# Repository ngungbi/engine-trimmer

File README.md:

# Engine Throttle Trimer

This device is used to adjust servo throttle for internal combustion engine from pixhawk output.

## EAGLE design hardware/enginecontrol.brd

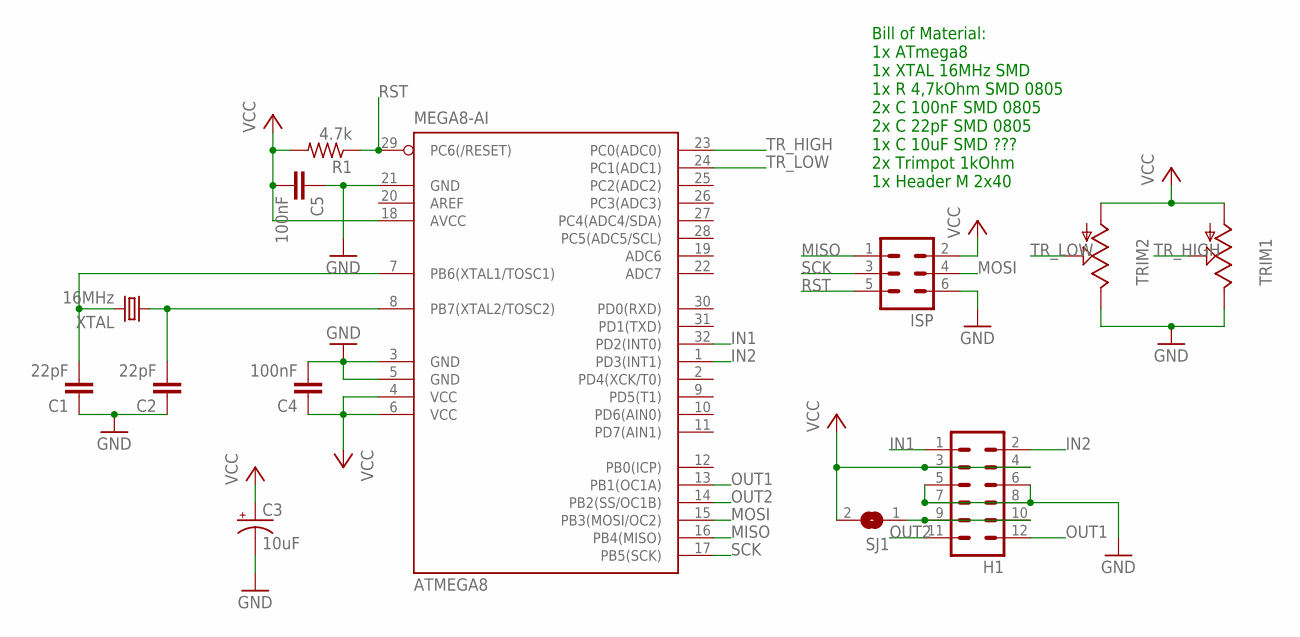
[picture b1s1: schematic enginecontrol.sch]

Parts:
ATMEGA8: MEGA8-AI; TQFP32-08
C1, C2: 22pF; C0805
C3: 10uF; 153CLV-0605
C4, C5: 100nF; C0805
H1: MA06-2
ISP: MA03-2
R1: 4.7k; M0805
SJ1: SJ
TRIM1, TRIM2: TRIM_US-B25P; B25P
XTAL: 16MHz; SM49

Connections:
GND: ATMEGA8.3 (GND), ATMEGA8.5 (GND), ATMEGA8.21 (GND), C1.1, C2.1, C3.-, C4.2, C5.1, H1.5, H1.6, H1.7, H1.8, ISP.6, TRIM1.E, TRIM2.E
IN1: ATMEGA8.32 (PD2(INT0)), H1.1
IN2: ATMEGA8.1 (PD3(INT1)), H1.2
MISO: ATMEGA8.16 (PB4(MISO)), ISP.1
MOSI: ATMEGA8.15 (PB3(MOSI/OC2)), ISP.4
unnamed: ATMEGA8.8 (PB7(XTAL2/TOSC2)), C2.2, XTAL.1
unnamed: ATMEGA8.7 (PB6(XTAL1/TOSC1)), C1.2, XTAL.2
unnamed: H1.9, H1.10, SJ1.1
OUT1: ATMEGA8.13 (PB1(OC1A)), H1.12
OUT2: ATMEGA8.14 (PB2(SS/OC1B)), H1.11
RST: ATMEGA8.29 (PC6(/RESET)), ISP.5, R1.1
SCK: ATMEGA8.17 (PB5(SCK)), ISP.3
TR_HIGH: ATMEGA8.23 (PC0(ADC0)), TRIM1.S
TR_LOW: ATMEGA8.24 (PC1(ADC1)), TRIM2.S
VCC: ATMEGA8.4 (VCC), ATMEGA8.6 (VCC), ATMEGA8.18 (AVCC), C3.+, C4.1, C5.2, H1.3, H1.4, ISP.2, R1.2, SJ1.2, TRIM1.A, TRIM2.A

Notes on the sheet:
Bill of Material: 1x ATmega8 1x XTAL 16MHz SMD 1x R 4,7kOhm SMD 0805 2x C 100nF SMD 0805 2x C 22pF SMD 0805 1x C 10uF SMD ??? 2x Trimpot 1kOhm 1x Header M 2x40

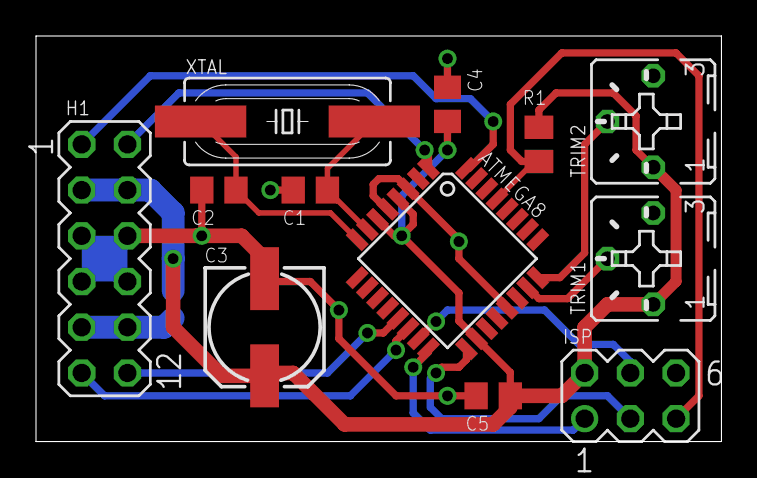
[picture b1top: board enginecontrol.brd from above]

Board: 2 copper layers, 38.1 x 22.5 mm, 13 parts (1 on the bottom side), 15 nets.

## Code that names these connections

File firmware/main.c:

#include <avr/io.h>
#include <avr/interrupt.h>
//#include <avr/eeprom.h>
#include <util/delay.h>
#include <stdint.h>
#include <stdio.h>

#include "adc.h"

#include "config.h"

//volatile uint8_t timerL = 0;
volatile uint8_t timerH = 0;
volatile uint16_t time0 = 0;
volatile uint16_t time1 = 0;

volatile uint16_t trimLow = 0;
volatile uint16_t trimHigh = 0;
volatile uint16_t range = 1000;

volatile uint16_t pwmIn = 2000;
volatile uint16_t pwmOut = 2000;

// manual PWM, adakah cara yang lebih baik? ._.
ISR(TIMER1_OVF_vect){
	PORTB |= (1<<2);
}
ISR(TIMER1_COMPA_vect){
	PORTB &= ~(1<<2);
}

// hitung pwm input
ISR(TIMER0_OVF_vect){
	timerH++;
}
ISR(INT0_vect){
	uint16_t timeNow = ((uint16_t)timerH<<8) | TCNT0;
	
	if( PIND&(1<<2) ){ // awal sinyal pwm
		PORTB |= (1<<1); // passthru
		time0 = timeNow;
	}else{ // akhir sinyal pwm
		PORTB &= ~(1<<1);
		time1 = timeNow;
		pwmIn = (time1-time0);

		// kasih batas nilai
		if(pwmIn<2000) pwmIn = 2000;
		else if(pwmIn>4000) pwmIn = 4000;

		// remap
		float value = (float)(pwmIn-2000)/2000.0 * range;
		pwmOut = (uint16_t)value + 2000 + trimLow;
		OCR1A = pwmOut;
	}
}

int main( void ){

	DDRB = 0x00;
	DDRC = 0x00;

	// input di PD2 dan PD3 (INT0, INT1)
	DDRD = 0x00;

	// output di PB1 dan PB2 (OCR1A, OCR1B)
	DDRB = (1<<1) | (1<<2);

	// pakai timer0 untuk hitung pwm input
	TCCR0=(0<<CS02) | (1<<CS01) | (0<<CS00);
	TCNT0=0x00;

	// manual pwm untuk output
	TCCR1A=(0<<COM1A1) | (0<<COM1A0) | (0<<COM1B1) | (0<<COM1B0) | (1<<WGM11) | (0<<WGM10);
	TCCR1B=(0<<ICNC1) | (0<<ICES1) | (1<<WGM13) | (1<<WGM12) | (0<<CS12) | (1<<CS11) | (0<<CS10);
	TCNT1=0x0000;
	ICR1=0x4E20; // overflow di 10ms
	OCR1A=0x0000;
	OCR1B=0x0000;

	TIMSK=(0<<OCIE2) | (0<<TOIE2) | (0<<TICIE1) | (1<<OCIE1A) | (0<<OCIE1B) | (1<<TOIE1) | (1<<TOIE0);

	// external interrupt di INT0 untuk baca pwm
	//PORTD |= 0x02;
	GICR|=(0<<INT1) | (1<<INT0);
	MCUCR=(0<<ISC11) | (0<<ISC10) | (0<<ISC01) | (1<<ISC00);
	GIFR=(0<<INTF1) | (1<<INTF0);
	
	ADC_Init();
	sei();
 	
 	PORTD |= (1<<3); // seharusnya untuk tombol input
 	OCR1A = 2000; // inisialisasi pwm 1000us

	while(1){
		//if(PIND&(1<<3)==0){
			// seharusnya jangan update setiap saat, hanya update saat tombol ditekan
			// tapi belum diimplementasi
			// dan seharusnya disimpan di eeprom :p
			trimLow  = ADC_Read(0);
			trimHigh = ADC_Read(1);
			range = 2000 - ( (trimHigh+trimLow)>>1 );
		//}
		
		_delay_ms(20);
	}
}

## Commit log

2018-01-08 sudah bisa remap input ke output
2018-01-08 siap untuk diuji
2018-01-08 add hardware
2018-01-08 merapikan kode
